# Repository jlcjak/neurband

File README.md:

# neurband

**An open, minimal sEMG wristband, like the Meta Neural Band.** Eight bipolar surface-EMG channels around the
wrist, a 24-bit biopotential front end, Bluetooth LE, and a module the size of a small watch face — designed
from first principles to record data good enough to train gesture models, and cheap enough to just build.

> **Status: design complete, not yet built.** Schematics, both PCBs (DRC-clean), mechanics, firmware
> (builds and links, untested on hardware), recorder and analysis code are done; everything below that says
> "simulated" or "estimated" has not been measured on a real board yet. See [what's next](#status-and-next-steps).

| | |
|---|---|
| Channels | 8 bipolar (P–N 20 mm along the forearm) + a driven bias pad in every pod |
| Front end | TI ADS1298, 24 bit, gain 6, 4 kSPS acquisition, ~1.2 µVrms (20–850 Hz) |
| Electrodes | 24 dry 6.5 mm ENIG gold pads on a 2-layer polyimide flex, foam-backed, 1 mm proud |
| Radio | nRF52832, BLE 5 2M PHY, printed antenna; 2 kSPS × 8 ch, 16-bit stream |
| IMU | LSM6DSL accel + gyro, 208 Hz |
| Power | 401223-class LiPo, about 130 mAh, ~12 h streaming (estimate); 2-pin magnetic charging connector in the module's end wall (charge with the band off the wrist) |
| Module | 31.6 × 37.1 × 9.65 mm body (48 mm across the strap bars), tapered and crowned, one size for 145–180 mm wrists |
| Strap | 20 mm hook-and-loop watch strap through two thick bars moulded into the base; the electrode pods snap onto it |
| Cost | ≈ $290–350 for a first build: 5 boards (2 assembled), 5 flexes, prints and off-the-shelf parts ([breakdown](docs/rev_c/cost.md)) |

## Gallery

| | |
|---|---|
|  |  |
|  |  |
|  |  |
|  |  |
|  |  |

The boards as laid out (KiCad renders, main board top and bottom; 28.7 × 27 mm):

| | |
|---|---|
|  |  |

All four copper layers (`python3 tools/copper_layers.py`):

A 1080 × 1350 turntable video is in [docs/media/turntable_r2.mp4](docs/media/turntable_r2.mp4).
All images are rendered from the real CAD and KiCad files with `python3 render/make_renders.py` (Blender Cycles);
see [docs/renders.md](docs/renders.md).

## How it works

```
 skin ─ 8 pods × (P, bias, N) gold pads ─ polyimide flex (GND-shielded) ─ 20-pin FPC
   └─ main board 28.7 × 27 mm, 4 layers, one-sided assembly
        ADS1298 ─ 16 × 10 kΩ inputs, bias amp (1 MΩ‖4.7 nF → all middle pads), filtered AVDD/2 reference
          │ SPI
        nRF52832 ─ printed 2.4 GHz antenna ─ BLE ─► nRF52840 USB dongle ─► host/neurband_ble.py ─► .npz
          ├ LSM6DSL IMU, button (wake/marker), LED
        LiPo ─ XC6206 3.3 V ─ RC filter ─ AVDD          magnetic charge connector ─ TP4054
```

Like Meta's research band (*A generic non-invasive neuromotor interface for
human-computer interaction*, Nature 2025), it has what matters: bipolar gold contacts 20 mm apart along the forearm, µV-level noise,
2 kHz data. It drops what only costs money: per-pod amplifiers, 16 channels, custom electrodes.
The reasoning, decision by decision, is in [docs/rev_c/README.md](docs/rev_c/README.md).

## The science, checked before building

Four independent reviews and simulations went into this design:

- **Signal chain** ([docs/science/signal_chain.md](docs/science/signal_chain.md)): noise budget, dry-contact
  impedance, mains pickup, sampling and BLE throughput, with pass/fail bench gates.
- **Circuit simulation** ([docs/science/simulations.md](docs/science/simulations.md), ngspice): bias-loop
  stability (57° worst-case phase margin), mains residual (≤ 1.5 µV on battery), RF filtering, radio-burst
  coupling — which is why the bias reference is filtered.
- **Forearm volume-conductor model** ([docs/science/emg_forward_model.md](docs/science/emg_forward_model.md)):
  a 3-D finite-difference model of the distal forearm (bones, muscles, fat, skin, anisotropic muscle), lead
  fields of all 8 channels, travelling motor-unit action potentials. 8 channels separate single muscles at
  98–100 %; pad size, spacing and band rotation are quantified.
- **Data & models** ([docs/science/data_and_models.md](docs/science/data_and_models.md)): what 8-channel wrist
  EMG can decode, how to use Meta's open datasets, a first-week recording protocol, and a working pipeline.

| | |
|---|---|
|  |  |

**Honest expectations** (per user, with calibration): 6–8 hand/wrist postures at ~90–98 %, pinches and thumb
swipes at ~75–90 %, 2-axis wrist control. Not expected: models that work across people without calibration,
typing, fluent handwriting.

## Build one

**Build guide: [docs/build/assembly.md](docs/build/assembly.md)**: the shopping list, the prints, ten
illustrated steps, troubleshooting and the tests to run on a first band (also as a
[PDF](docs/build/neurband_build_manual.pdf)). There is also a 36 s
[assembly animation](docs/media/assembly_r2.mp4).

A first prototype costs around $300 (≈ $290–350 for five main boards with two assembled, five electrode flexes,
the prints and the off-the-shelf parts; [breakdown](docs/rev_c/cost.md)). Most of it is the ADS1298 and the
fab's assembly fees.

1. **Order** two things:
   - the assembled main board, the electrode flex and the prints, with **Buy it** in Backplane
     (`boards/neurband_c/ORDERING.md`, `boards/neurband_c_flex/ORDERING.md`, `mech/rev_c/*.fab.json`);
   - about EUR 75 of off-the-shelf parts ([docs/build/sourcing.md](docs/build/sourcing.md)): a 20 mm
     hook-and-loop watch strap, 6 mm foam dots, a 401223 LiPo, a 2-pin magnetic charging connector and
     cable, a Pico 2 as the SWD probe and an nRF52840 dongle.
2. **Build** it ([docs/build/assembly.md](docs/build/assembly.md), PDF alongside):
   - flash the bare board once through four soldered wires on the SWD pads (3V3, SWDIO, SWDCLK, GND);
   - solder the cell and the charging connector;
   - bond the six free pods in the flat jig and the base in the pedestal jig;
   - fold the tail into J1 and close the module;
   - snap the strap into the pods, lock one end on bar A, tighten through bar B.

   Design details are in [docs/mech/mechanical_c.md](docs/mech/mechanical_c.md).
3. **Record**: `python3 host/neurband_ble.py -o rec.npz`, and in a second terminal
   `python3 -m analysis collect basic --out data/s1`.
4. **Check and train**: `python3 -m analysis report data/*.npz`, `python3 -m analysis train data/*.npz`.
   Try the whole pipeline without hardware: `python3 -m analysis synth /tmp/nb`.

**Safety.** Wear it only while it runs on its own battery. Never connect a charger, USB cable, debugger or
grounded instrument while the pads touch skin. This is a research prototype, not a medical device.

## Repository

| Path | What |
|---|---|
| `boards/neurband_c/` | main board: schematic generator (`gen_c_sch.py`), KiCad project, layout scripts |
| `boards/neurband_c_flex/` | electrode flex: schematic + parametric PCB generator |
| `mech/rev_c/` | FreeCAD scripts and STEP for the module, pods, strap path, bonding jigs and fit checks |
| `firmware_c/` | nRF52832 Zephyr firmware |
| `host/` | BLE recorder and packet tests |
| `analysis/` | quality gates, features, baseline models, collection prompts, Meta dataset reader |
| `sim/` | ngspice AFE simulations and the forearm EMG forward model |
| `render/` | Blender pipeline for the images (`python3 render/make_renders.py`) |
| `docs/` | design notes, reviews, science, layout and mechanical docs |
| `.archive/` | older work (a dot-folder, so Backplane's project list skips it): rev A (16 ch, ESP32, 54 × 34 mm) and rev B boards, rev A/B mechanics, the rev C layout scripts |
| `tools/` | the small Python KiCad schematic generator used for every schematic |

## Status and next steps

- [x] Rev C schematic, main board (DRC 0), flex (DRC 0), mechanics, fit checks on 145/160/180 mm wrists
- [x] Firmware builds and links for the nRF52832 (Zephyr 4.4.2, 0 warnings, 30 % flash / 94 % RAM); host recorder and analysis pipeline tested on synthetic data
- [x] Pre-order review and rework: analog coupling/noise ([analog_preorder_review.md](docs/review/analog_preorder_review.md)), on-wrist antenna FDTD simulation ([antenna_sim.md](docs/science/antenna_sim.md)), manufacturing and pick-and-place check against the fab's own footprints ([manufacturing_preorder.md](docs/review/manufacturing_preorder.md)), layout owner's review ([sol_preorder_review.md](docs/review/sol_preorder_review.md)), assembly walk-through ([assembly.md](docs/build/assembly.md))
- [ ] Build two boards; bench gates: shorted-input noise, mains residual, radio-on noise, bias-loop stability
- [ ] Antenna tuning (π network on the board), BLE throughput on a real link
- [ ] First week of recordings with the protocol in `docs/science/data_and_models.md`

## Credits

Research summary of Meta's work in [docs/research/meta_semg_research.md](docs/research/meta_semg_research.md).
Human model: Blender Studio "Human Base Meshes" (CC0). KiCad stock libraries. Meta's datasets referenced here are
CC BY-NC 4.0.

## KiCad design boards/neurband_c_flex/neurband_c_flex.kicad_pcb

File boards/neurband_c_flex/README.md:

# Electrode flex, rev C

| File | What it is |
|---|---|
| `neurband_c_flex.kicad_pro` / `.kicad_pcb` / `.kicad_sch` | The KiCad project (generated) |
| `gen_flex_c_pcb.py`, `gen_flex_c_sch.py`, `flex_pinmap.py`, `requirements.txt` | The generators and the pod-to-finger map; edit these, not the board |
| `ORDERING.md` | What the flex order must be (ordered with **Buy it**; `neurband_c_flex.fab.json` is `kind: flex`) |
| `neurband_c_flex.step`, `renders/` | 3D model and images |
| `neurband_c_flex.pretty`, `.kicad_dru`, `fp-lib-table` | Footprints and design rules the board needs |

Layout notes: [docs/layout/flex_c_layout.md](../../docs/layout/flex_c_layout.md).

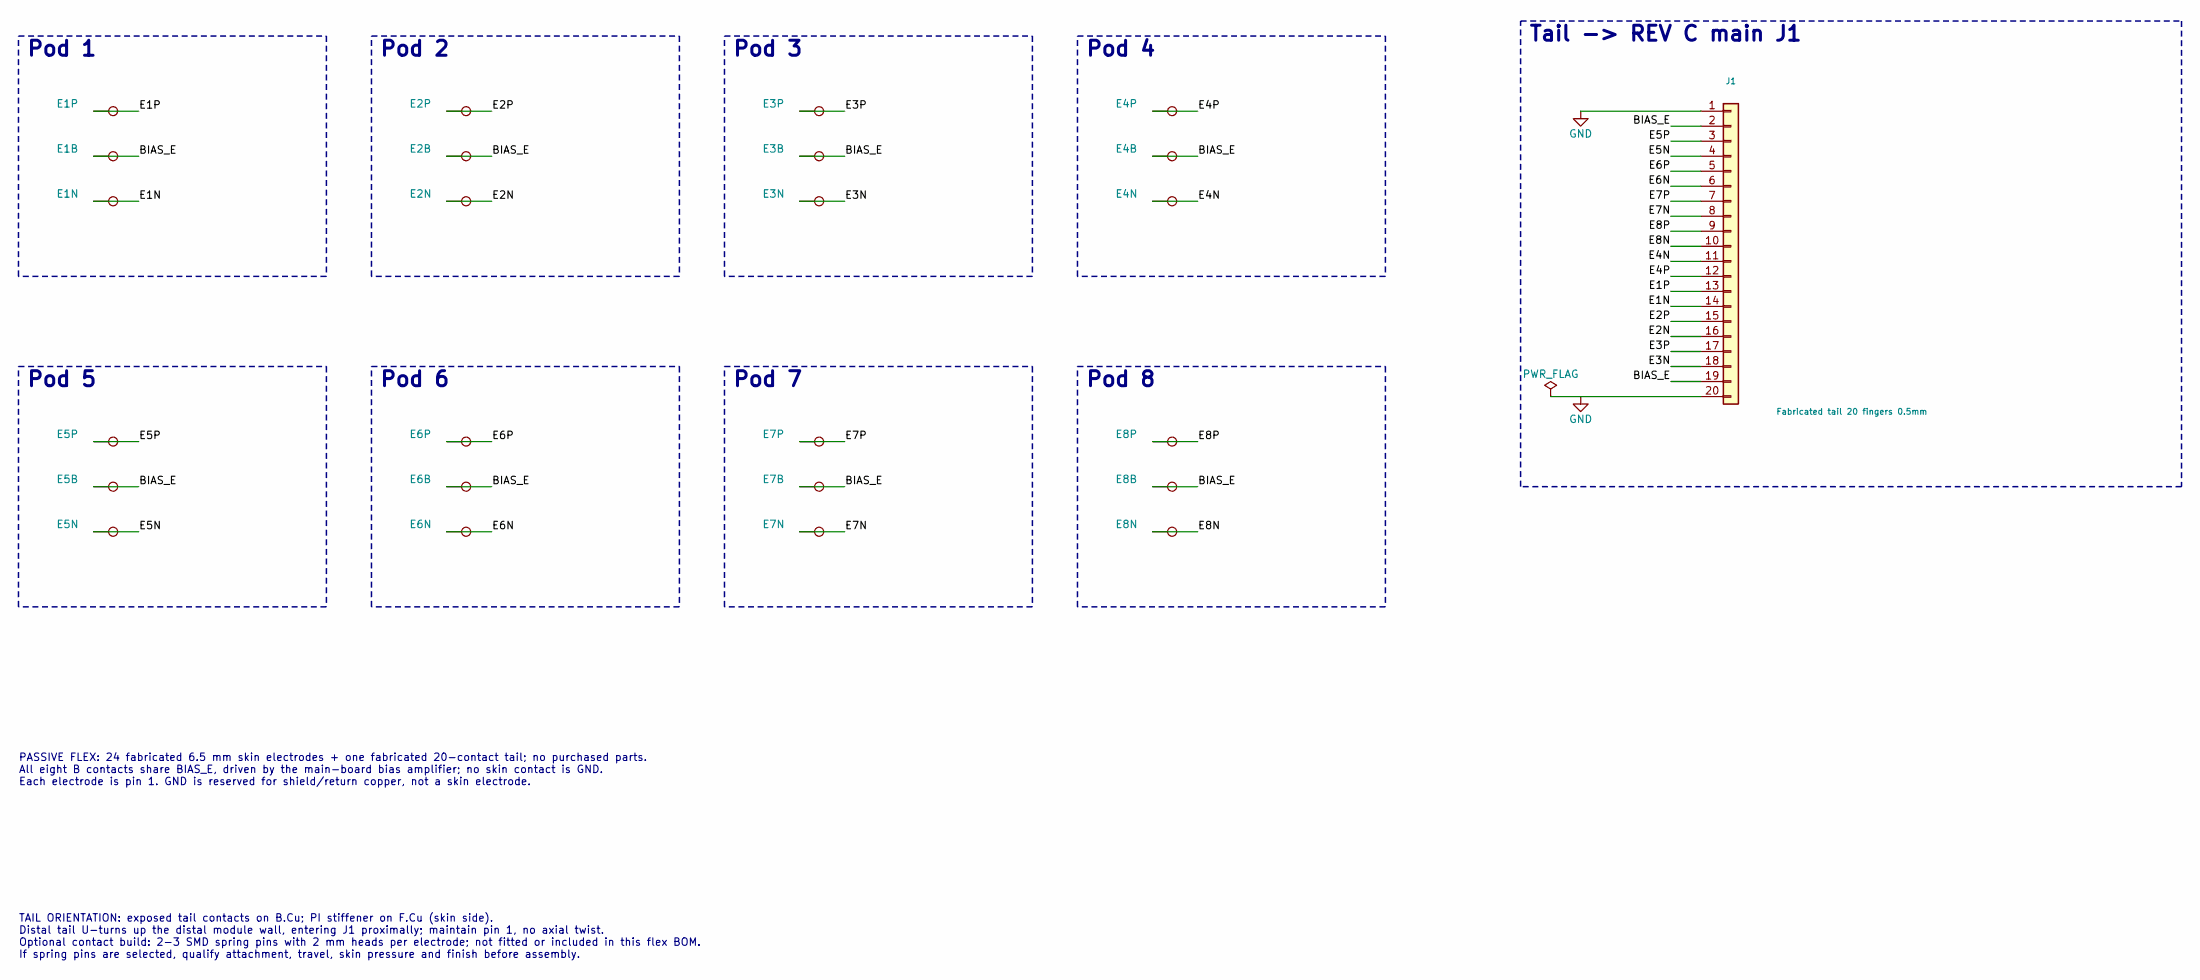
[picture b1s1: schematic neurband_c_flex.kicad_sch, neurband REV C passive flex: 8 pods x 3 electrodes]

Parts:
E1B, E2B, E3B, E4B, E5B, E6B, E7B, E8B: Fabricated electrode B; Electrode_D6.5mm
E1N, E2N, E3N, E4N, E5N, E6N, E7N, E8N: Fabricated electrode N; Electrode_D6.5mm
E1P, E2P, E3P, E4P, E5P, E6P, E7P, E8P: Fabricated electrode P; Electrode_D6.5mm
J1: Fabricated tail 20 fingers 0.5mm; FPC_Tail_20_P0.5mm

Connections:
/BIAS_E: E1B.1, E2B.1, E3B.1, E4B.1, E5B.1, E6B.1, E7B.1, E8B.1, J1.2, J1.19
/E1N: E1N.1, J1.14
/E1P: E1P.1, J1.13
/E2N: E2N.1, J1.16
/E2P: E2P.1, J1.15
/E3N: E3N.1, J1.18
/E3P: E3P.1, J1.17
/E4N: E4N.1, J1.11
/E4P: E4P.1, J1.12
/E5N: E5N.1, J1.4
/E5P: E5P.1, J1.3
/E6N: E6N.1, J1.6
/E6P: E6P.1, J1.5
/E7N: E7N.1, J1.8
/E7P: E7P.1, J1.7
/E8N: E8N.1, J1.10
/E8P: E8P.1, J1.9
GND: J1.1, J1.20

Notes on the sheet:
Tail -> REV C main J1
Pod 1
Pod 2
Pod 3
Pod 4
Pod 5
Pod 6
Pod 7
Pod 8
PASSIVE FLEX: 24 fabricated 6.5 mm skin electrodes + one fabricated 20-contact tail; no purchased parts. All eight B contacts share BIAS_E, driven by the main-board bias amplifier; no skin contact is GND. Each electrode is pin 1. GND is reserved for shield/return copper, not a skin electrode.
TAIL ORIENTATION: exposed tail contacts on B.Cu; PI stiffener on F.Cu (skin side). Distal tail U-turns up the distal module wall, entering J1 proximally; maintain pin 1, no axial twist. Optional contact build: 2-3 SMD spring pins with 2 mm heads per electrode; not fitted or included in this flex BO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

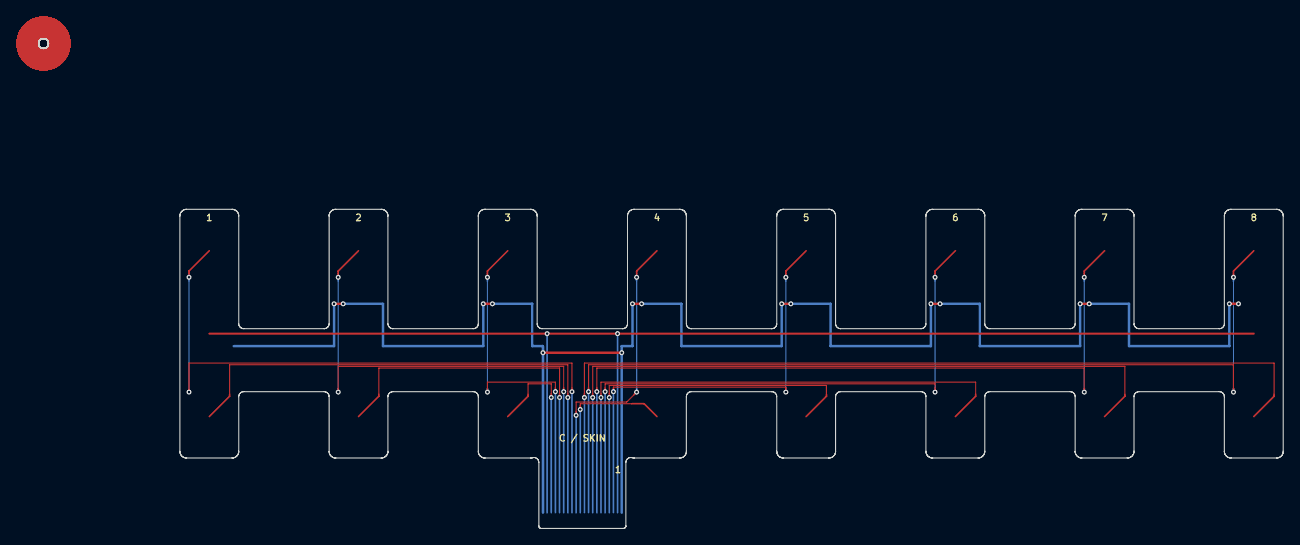
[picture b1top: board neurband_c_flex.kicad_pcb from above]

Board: 2 copper layers, 133.1 x 38.5 mm, 41 parts (1 on the bottom side), 18 nets.

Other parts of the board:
H10, H11, H20, H21, H30, H31, H40, H41, H50, H51, H60, H61, H70, H71, H80, H81: Alignment 1.2mm; Alignment_D1.2mm

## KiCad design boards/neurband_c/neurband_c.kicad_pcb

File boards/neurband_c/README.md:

# Main board, rev C

| File | What it is |
|---|---|
| `neurband_c.kicad_pro` / `.kicad_pcb` / `.kicad_sch` | The KiCad project. Open the `.kicad_pro` |
| `gen_c_sch.py` | Generates the schematic (`python3 gen_c_sch.py`); edit this, not the `.kicad_sch` |
| `ORDERING.md`, `neurband_c.fab.json` | How the board is ordered (**Buy it**) |
| `neurband_c_bom.csv` | Bill of materials with MPNs and the fab's part numbers |
| `neurband_c.step`, `neurband_c_board_only.step` | 3D models, with and without parts |
| `renders/` | Top, bottom, 3D and per-layer images |
| `layout/neurband.pretty`, `layout/models` | Local footprints and 3D models the board needs |
| `layout/*.md`, `layout/preorder_release.json`, `layout/XUNPU_*` | Evidence: RF geometry, J1 connector review, release checks |

Layout notes: [docs/layout/main_c_layout.md](../../docs/layout/main_c_layout.md). The scripts used while
laying it out are in [.archive/neurband_c_layout_scripts](../../.archive/neurband_c_layout_scripts/).

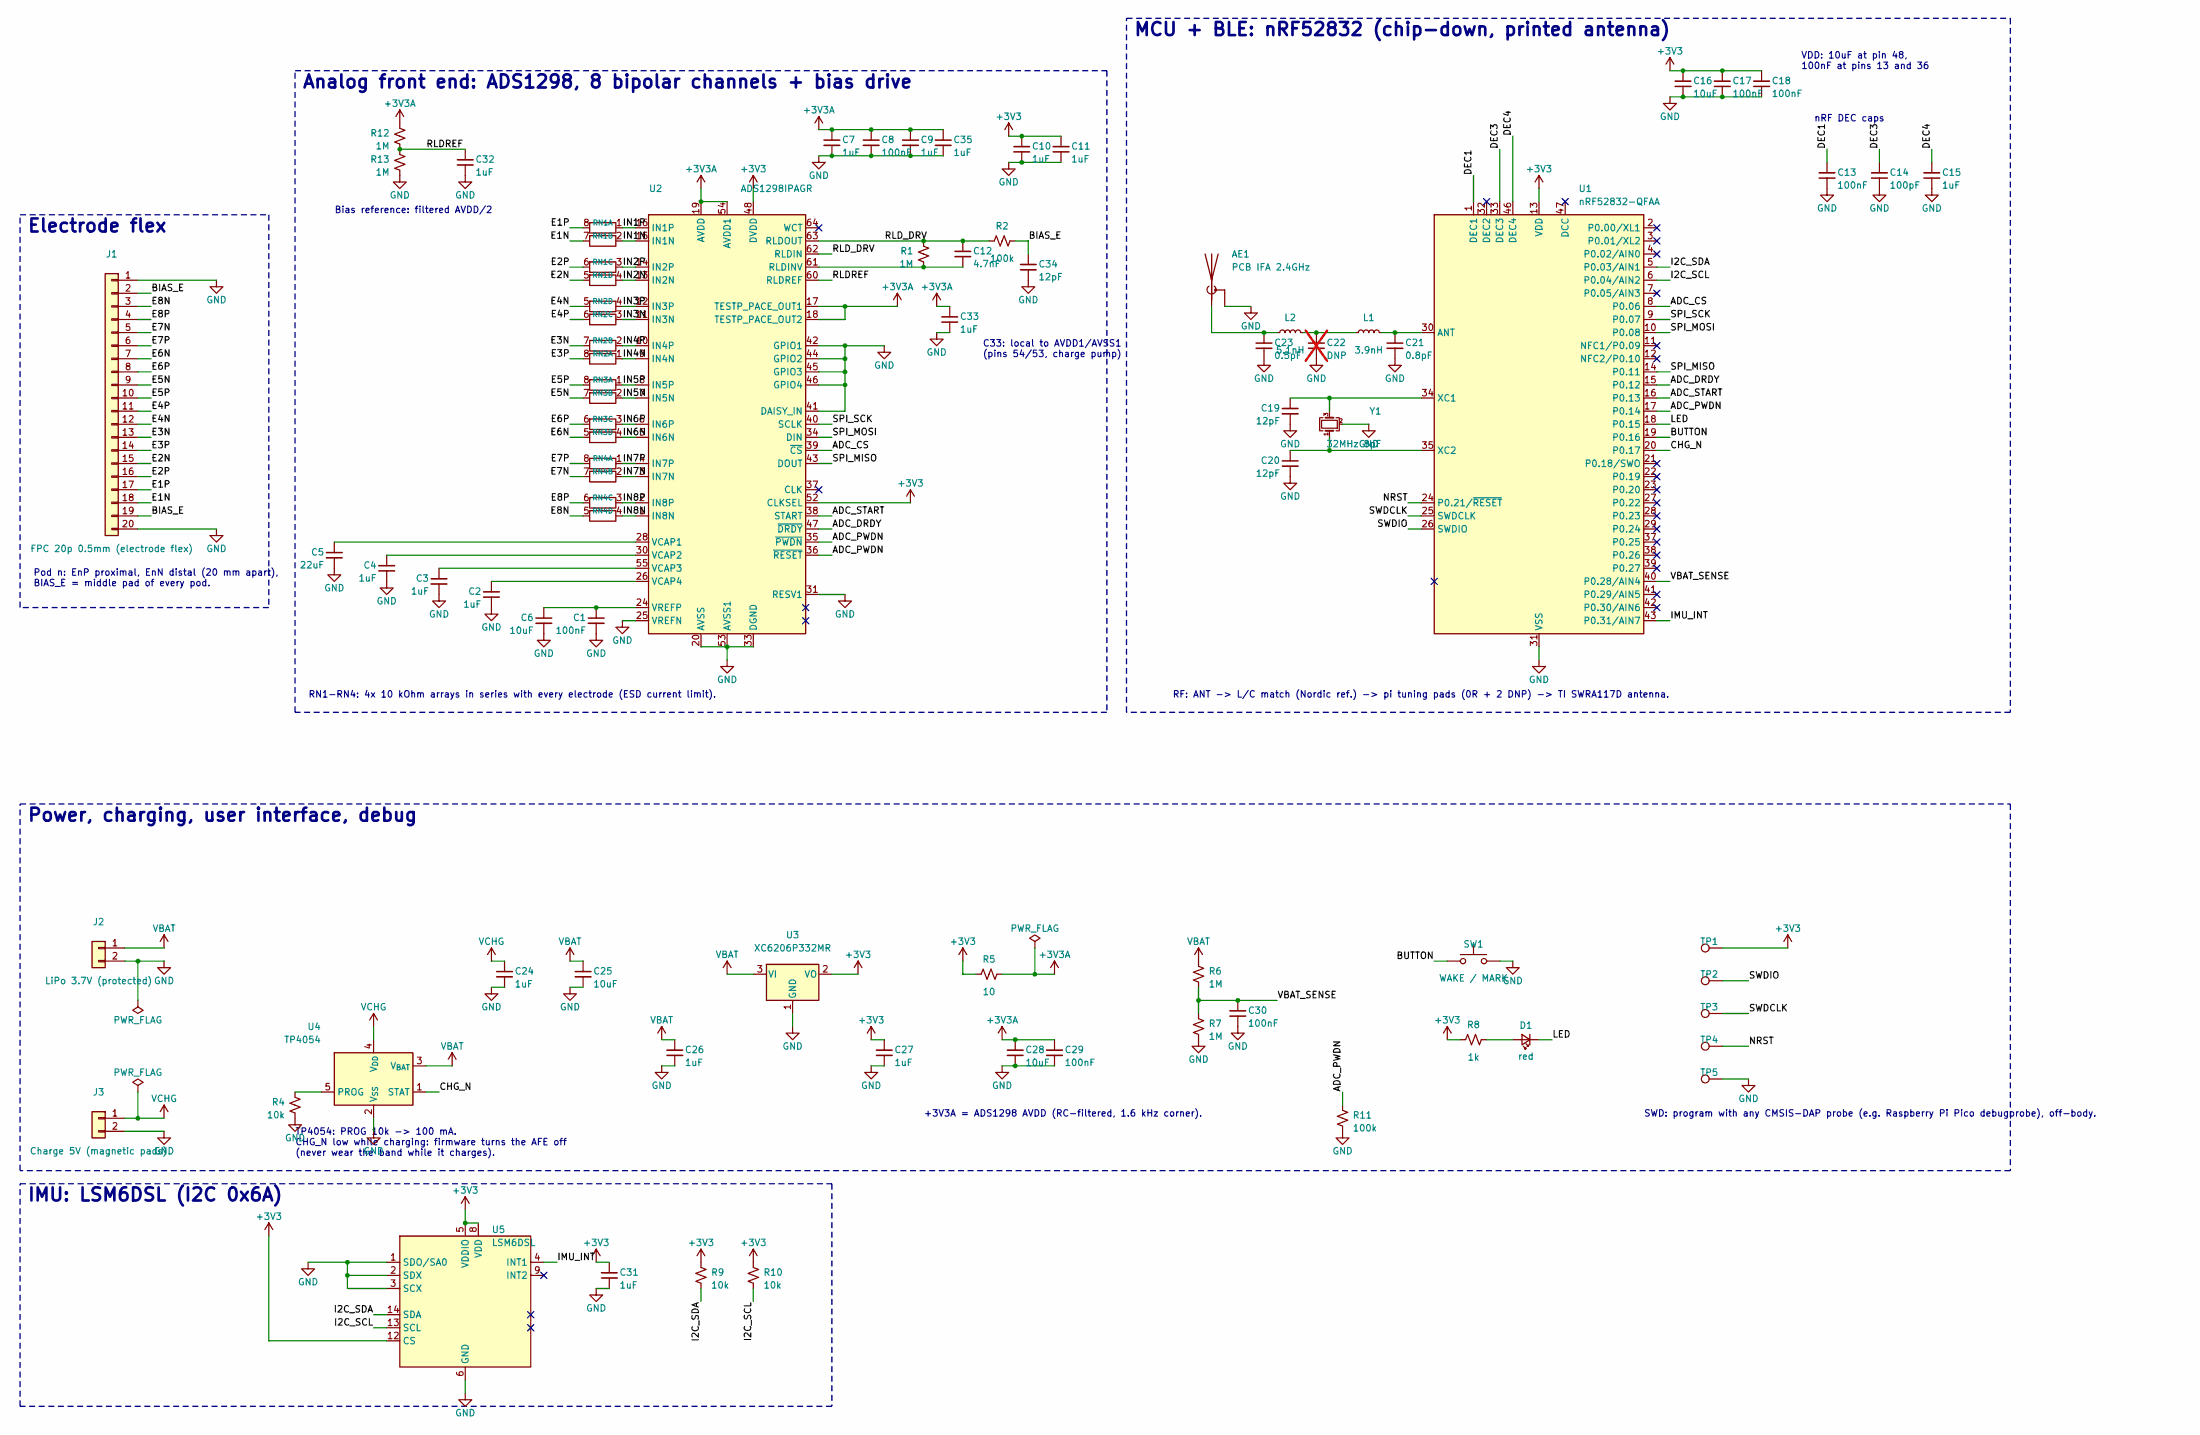
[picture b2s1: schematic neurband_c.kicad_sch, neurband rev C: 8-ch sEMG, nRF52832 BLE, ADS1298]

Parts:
AE1: PCB IFA 2.4GHz; Texas_SWRA117D_2.4GHz_Left
C1, C8, C13, C17, C18, C29, C30: 100nF; C_0402_Small; MPN CL05B104KO5NNNC; LCSC C1525
C2, C3, C4, C7, C9, C10, C11, C15, C24, C26, C27, C31, C32, C33, C35: 1uF; C_0402_Small; MPN CL05A105KA5NQNC; LCSC C52923
C5: 22uF; C_0603_Small; MPN CL10A226MQ8NRNC; LCSC C59461
C6, C16, C25, C28: 10uF; C_0603_Small; MPN CL10A106KP8NNNC; LCSC C19702
C12: 4.7nF; C_0402_Small; MPN 0402B472K500NT; LCSC C1538
C14: 100pF; C_0402_Small; MPN 0402CG101J500NT; LCSC C1546
C19, C20, C34: 12pF; C_0402_Small; MPN 0402CG120J500NT; LCSC C1547
C21: 0.8pF; C_0402_Small; MPN 0402CG0R8B500NT; LCSC C285068
C22: DNP; C_0402_Small; not fitted
C23: 0.5pF; C_0402_Small; MPN 0402CG0R5B500NT; LCSC C285052
D1: red; LED_0603_1608Metric; MPN KT-0603R; LCSC C2286
J1: FPC 20p 0.5mm (electrode flex); XUNPU_FPC-05F-20PH20_Centroid; MPN FPC-05F-20PH20; LCSC C2856803
J2: LiPo 3.7V (protected); WirePads_2x1.5x2mm_P3mm
J3: Charge 5V (magnetic pads); WirePads_2x1.5x2mm_P3mm
L1: 3.9nH; L_0402_Small; MPN SDCL1005C3N9STDF; LCSC C14033
L2: 5.1nH; L_0402_Small; MPN SDCL1005C5N1STDF; LCSC C33114
R1, R6, R7, R12, R13: 1M; R_0402_Small; MPN 0402WGF1004TCE; LCSC C26083
R2, R11: 100k; R_0402_Small; MPN 0402WGF1003TCE; LCSC C25741
R4, R9, R10: 10k; R_0402_Small; MPN 0402WGF1002TCE; LCSC C25744
R5: 10; R_0402_Small; MPN 0402WGF100JTCE; LCSC C25077
R8: 1k; R_0402_Small; MPN 0402WGF1001TCE; LCSC C11702
RN1, RN2, RN3, RN4: 10k; R_Array_Convex_4x0603_FabZero; MPN 4D03WGJ0103T5E; LCSC C29718
SW1: WAKE / MARK; SW_SPST_TS-1088-xR020; MPN TS-1088-AR02016; LCSC C720477
TP1, TP2, TP3, TP4, TP5: pad; SWD_Pad_1x1_P1.27
U1: nRF52832-QFAA; QFN-48-1EP_6x6mm_P0.4mm_EP4.6x4.6mm_FabZero; MPN NRF52832-QFAA-R; LCSC C77540
U2: ADS1298IPAGR; TQFP-64_10x10mm_P0.5mm_FabZero; MPN ADS1298IPAGR; LCSC C527440
U3: XC6206P332MR; SOT-23-3_FabZero; MPN XC6206P332MR-G; LCSC C5446
U4: TP4054; SOT-23-5_FabZero; MPN TP4054-42-SOT25R; LCSC C32574
U5: LSM6DSL; LGA-14_3x2.5mm_P0.5mm_LayoutBorder3x4y; MPN LSM6DSLTR; LCSC C126672
Y1: 32MHz 8pF; Crystal_SMD_2016-4Pin_2.0x1.6mm; MPN X201632MKB4SI; LCSC C718072

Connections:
+3V3: C10.1, C11.1, C16.1, C17.1, C18.1, C27.1, C31.1, R5.1, R8.1, R9.1, R10.1, TP1.1 (1_1), U1.13 (VDD), U1.36 (VDD), U1.48 (VDD), U2.48 (DVDD), U2.50 (DVDD), U2.52 (CLKSEL), U3.2 (VO), U5.5 (VDDIO), U5.8 (VDD), U5.12 (CS)
+3V3A: C7.1, C8.1, C9.1, C28.1, C29.1, C33.1, C35.1, R5.2, R12.1, U2.17 (TESTP_PACE_OUT1), U2.18 (TESTP_PACE_OUT2), U2.19 (AVDD), U2.21 (AVDD), U2.22 (AVDD), U2.54 (AVDD1), U2.56 (AVDD), U2.59 (AVDD)
/ADC_CS: U1.8 (P0.06), U2.39 (~CS)
/ADC_DRDY: U1.15 (P0.12), U2.47 (~DRDY)
/ADC_PWDN: R11.1, U1.17 (P0.14), U2.35 (~PWDN), U2.36 (~RESET)
/ADC_START: U1.16 (P0.13), U2.38 (START)
/BIAS_E: C34.1, J1.2, J1.19, R2.2
/BUTTON: SW1.1, U1.19 (P0.16)
/CHG_N: U1.20 (P0.17), U4.1 (STAT)
/DEC1: C13.1, U1.1 (DEC1)
/DEC3: C14.1, U1.33 (DEC3)
/DEC4: C15.1, U1.46 (DEC4)
/E1N: J1.18, RN1.7 (R2.2)
/E1P: J1.17, RN1.8 (R1.2)
/E2N: J1.15, RN1.5 (R4.2)
/E2P: J1.16, RN1.6 (R3.2)
/E3N: J1.13, RN2.7 (R2.2)
/E3P: J1.14, RN2.8 (R1.2)
/E4N: J1.12, RN2.5 (R4.2)
/E4P: J1.11, RN2.6 (R3.2)
/E5N: J1.9, RN3.7 (R2.2)
/E5P: J1.10, RN3.8 (R1.2)
/E6N: J1.7, RN3.5 (R4.2)
/E6P: J1.8, RN3.6 (R3.2)
/E7N: J1.5, RN4.7 (R2.2)
/E7P: J1.6, RN4.8 (R1.2)
/E8N: J1.3, RN4.5 (R4.2)
/E8P: J1.4, RN4.6 (R3.2)
/I2C_SCL: R10.2, U1.6 (P0.04/AIN2), U5.13 (SCL)
/I2C_SDA: R9.2, U1.5 (P0.03/AIN1), U5.14 (SDA)
/IMU_INT: U1.43 (P0.31/AIN7), U5.4 (INT1)
/IN1N: RN1.2 (R2.1), U2.15 (IN1N)
/IN1P: RN1.1 (R1.1), U2.16 (IN1P)
/IN2N: RN1.4 (R4.1), U2.13 (IN2N)
/IN2P: RN1.3 (R3.1), U2.14 (IN2P)
/IN3N: RN2.3 (R3.1), U2.11 (IN3N)
/IN3P: RN2.4 (R4.1), U2.12 (IN3P)
/IN4N: RN2.1 (R1.1), U2.9 (IN4N)
/IN4P: RN2.2 (R2.1), U2.10 (IN4P)
/IN5N: RN3.2 (R2.1), U2.7 (IN5N)
/IN5P: RN3.1 (R1.1), U2.8 (IN5P)
/IN6N: RN3.4 (R4.1), U2.5 (IN6N)
/IN6P: RN3.3 (R3.1), U2.6 (IN6P)
/IN7N: RN4.2 (R2.1), U2.3 (IN7N)
/IN7P: RN4.1 (R1.1), U2.4 (IN7P)
/IN8N: RN4.4 (R4.1), U2.1 (IN8N)
/IN8P: RN4.3 (R3.1), U2.2 (IN8P)
/LED: D1.1 (K), U1.18 (P0.15)
/NRST: TP4.1 (1_1), U1.24 (P0.21/~RESET)
/RLDREF: C32.1, R12.2, R13.1, U2.60 (RLDREF)
/RLD_DRV: C12.1, R1.1, R2.1, U2.62 (RLDIN), U2.63 (RLDOUT)
/SPI_MISO: U1.14 (P0.11), U2.43 (DOUT)
/SPI_MOSI: U1.10 (P0.08), U2.34 (DIN)
/SPI_SCK: U1.9 (P0.07), U2.40 (SCLK)
/SWDCLK: TP3.1 (1_1), U1.25 (SWDCLK)
/SWDIO: TP2.1 (1_1), U1.26 (SWDIO)
/VBAT_SENSE: C30.1, R6.2, R7.1, U1.40 (P0.28/AIN4)
GND: AE1.2 (Shield), C1.2, C2.2, C3.2, C4.2, C5.2, C6.2, C7.2, C8.2, C9.2, C10.2, C11.2, C13.2, C14.2, C15.2, C16.2, C17.2, C18.2, C19.2, C20.2, C21.2, C22.2, C23.2, C24.2, C25.2, C26.2, C27.2, C28.2, C29.2, C30.2, C31.2, C32.2, C33.2, C34.2, C35.2, J1.1, J1.20, J2.2, J3.2, R4.2, R7.2, R11.2, R13.2, SW1.2, TP5.1 (1_1), U1.31 (VSS), U1.45 (VSS), U1.49 (VSS), U2.20 (AVSS), U2.23 (AVSS), U2.25 (VREFN), U2.31 (RESV1), U2.32 (AVSS), U2.33 (DGND), U2.41 (DAISY_IN), U2.42 (GPIO1), U2.44 (GPIO2), U2.45 (GPIO3), U2.46 (GPIO4), U2.49 (DGND), U2.51 (DGND), U2.53 (AVSS1), U2.57 (AVSS), U2.58 (AVSS), U3.1 (GND), U4.2 (V_{SS}), U5.1 (SDO/SA0), U5.2 (SDX), U5.3 (SCX), U5.6 (GND), U5.7 (GND), Y1.2 (G), Y1.4 (G)
unnamed: AE1.1 (A), C23.1, L2.1
unnamed: C22.1, L1.1, L2.2
unnamed: D1.2 (A), R8.2
unnamed: C21.1, L1.2, U1.30 (ANT)
unnamed: C19.1, U1.34 (XC1), Y1.3
unnamed: C20.1, U1.35 (XC2), Y1.1
unnamed: C12.2, R1.2, U2.61 (RLDINV)
unnamed: C5.1, U2.28 (VCAP1)
unnamed: C4.1, U2.30 (VCAP2)
unnamed: C3.1, U2.55 (VCAP3)
unnamed: C2.1, U2.26 (VCAP4)
unnamed: C1.1, C6.1, U2.24 (VREFP)
unnamed: R4.1, U4.5 (PROG)
VBAT: C25.1, C26.1, J2.1, R6.1, U3.3 (VI), U4.3 (V_{BAT})
VCHG: C24.1, J3.1, U4.4 (V_{DD})

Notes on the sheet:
Analog front end: ADS1298, 8 bipolar channels + bias drive
C33: local to AVDD1/AVSS1 (pins 54/53, charge pump)
VDD: 10uF at pin 48, 100nF at pins 13 and 36
nRF DEC caps
MCU + BLE: nRF52832 (chip-down, printed antenna)
TP4054: PROG 10k -> 100 mA. CHG_N low while charging: firmware turns the AFE off (never wear the band while it charges).
IMU: LSM6DSL (I2C 0x6A)
Pod n: EnP proximal, EnN distal (20 mm apart), BIAS_E = middle pad of every pod.
Bias reference: filtered AVDD/2
RN1-RN4: 4x 10 kOhm arrays in series with every electrode (ESD current limit).
Electrode flex
Power, charging, user interface, debug
+3V3A = ADS1298 AVDD (RC-filtered, 1.6 kHz corner).
SWD: program with any CMSIS-DAP probe (e.g. Raspberry Pi Pico debugprobe), off-body.
RF: ANT -> L/C match (Nordic ref.) -> pi tuning pads (0R + 2 DNP) -> TI SWRA117D antenna.

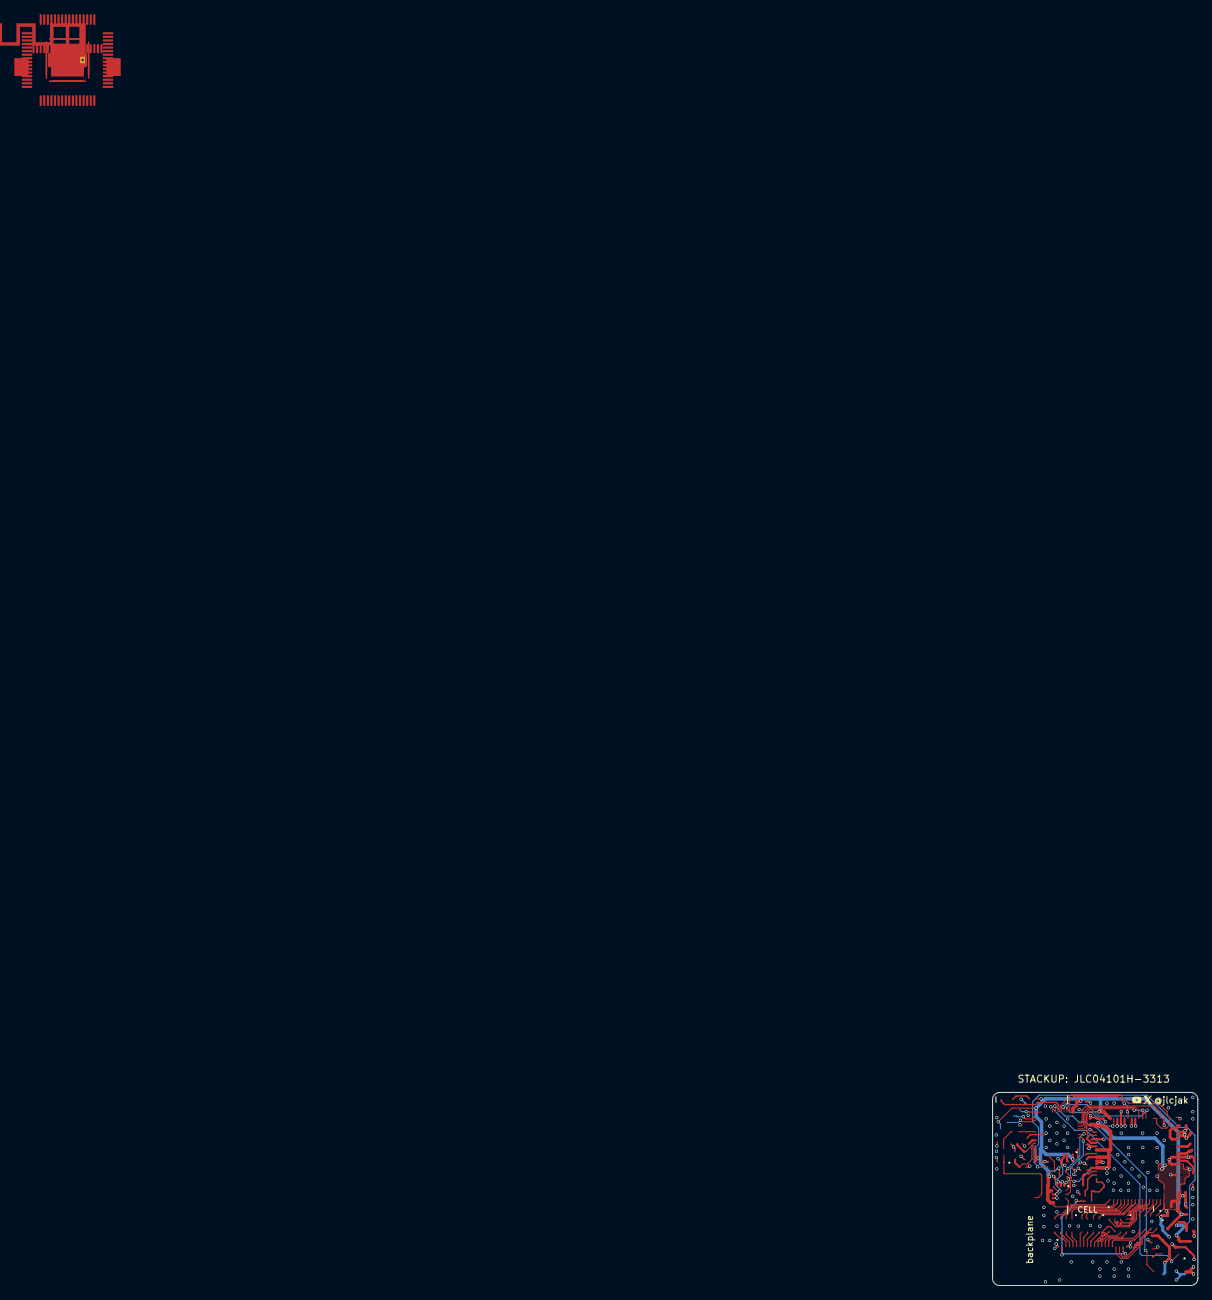
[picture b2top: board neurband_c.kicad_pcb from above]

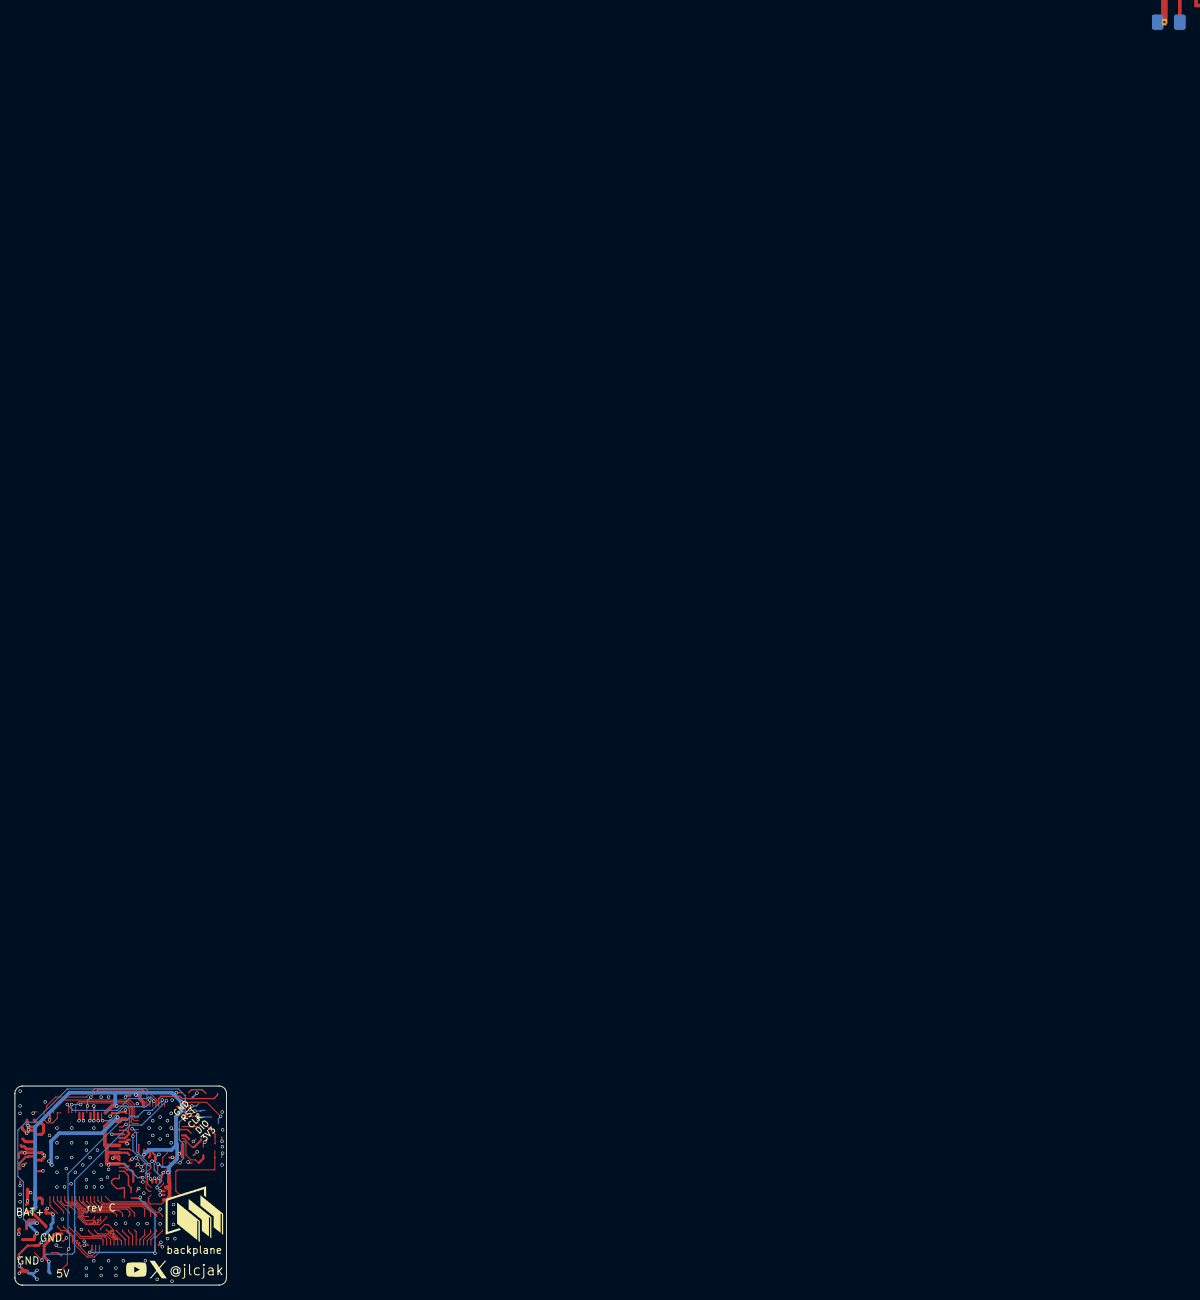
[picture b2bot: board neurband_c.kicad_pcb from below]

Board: 4 copper layers, 28.7 x 27.0 mm, 70 parts (7 on the bottom side), 73 nets.

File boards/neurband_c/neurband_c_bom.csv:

"Reference","Value","Footprint","MPN","LCSC","QUANTITY"
"C1,C8,C13,C17,C18,C29,C30","100nF","neurband:C_0402_Small","CL05B104KO5NNNC","C1525","7"
"C2-C4,C7,C9-C11,C15,C24,C26,C27,C31-C33,C35","1uF","neurband:C_0402_Small","CL05A105KA5NQNC","C52923","15"
"C5","22uF","neurband:C_0603_Small","CL10A226MQ8NRNC","C59461","1"
"C6,C16,C25,C28","10uF","neurband:C_0603_Small","CL10A106KP8NNNC","C19702","4"
"C12","4.7nF","neurband:C_0402_Small","0402B472K500NT","C1538","1"
"C14","100pF","neurband:C_0402_Small","0402CG101J500NT","C1546","1"
"C19,C20,C34","12pF","neurband:C_0402_Small","0402CG120J500NT","C1547","3"
"C21","0.8pF","neurband:C_0402_Small","0402CG0R8B500NT","C285068","1"
"C23","0.5pF","neurband:C_0402_Small","0402CG0R5B500NT","C285052","1"
"D1","red","LED_SMD:LED_0603_1608Metric","KT-0603R","C2286","1"
"J1","FPC 20p 0.5mm (electrode flex)","neurband:XUNPU_FPC-05F-20PH20_Centroid","FPC-05F-20PH20","C2856803","1"
"L1","3.9nH","neurband:L_0402_Small","SDCL1005C3N9STDF","C14033","1"
"L2","5.1nH","neurband:L_0402_Small","SDCL1005C5N1STDF","C33114","1"
"R1,R6,R7,R12,R13","1M","neurband:R_0402_Small","0402WGF1004TCE","C26083","5"
"R2,R11","100k","neurband:R_0402_Small","0402WGF1003TCE","C25741","2"
"R4,R9,R10","10k","neurband:R_0402_Small","0402WGF1002TCE","C25744","3"
"R5","10","neurband:R_0402_Small","0402WGF100JTCE","C25077","1"
"R8","1k","neurband:R_0402_Small","0402WGF1001TCE","C11702","1"
"RN1-RN4","10k","neurband:R_Array_Convex_4x0603_FabZero","4D03WGJ0103T5E","C29718","4"
"SW1","WAKE / MARK","Button_Switch_SMD:SW_SPST_TS-1088-xR020","TS-1088-AR02016","C720477","1"
"U1","nRF52832-QFAA","neurband:QFN-48-1EP_6x6mm_P0.4mm_EP4.6x4.6mm_FabZero","NRF52832-QFAA-R","C77540","1"
"U2","ADS1298IPAGR","neurband:TQFP-64_10x10mm_P0.5mm_FabZero","ADS1298IPAGR","C527440","1"
"U3","XC6206P332MR","neurband:SOT-23-3_FabZero","XC6206P332MR-G","C5446","1"
"U4","TP4054","neurband:SOT-23-5_FabZero","TP4054-42-SOT25R","C32574","1"
"U5","LSM6DSL","Package_LGA:LGA-14_3x2.5mm_P0.5mm_LayoutBorder3x4y","LSM6DSLTR","C126672","1"
"Y1","32MHz 8pF","Crystal:Crystal_SMD_2016-4Pin_2.0x1.6mm","X201632MKB4SI","C718072","1"
